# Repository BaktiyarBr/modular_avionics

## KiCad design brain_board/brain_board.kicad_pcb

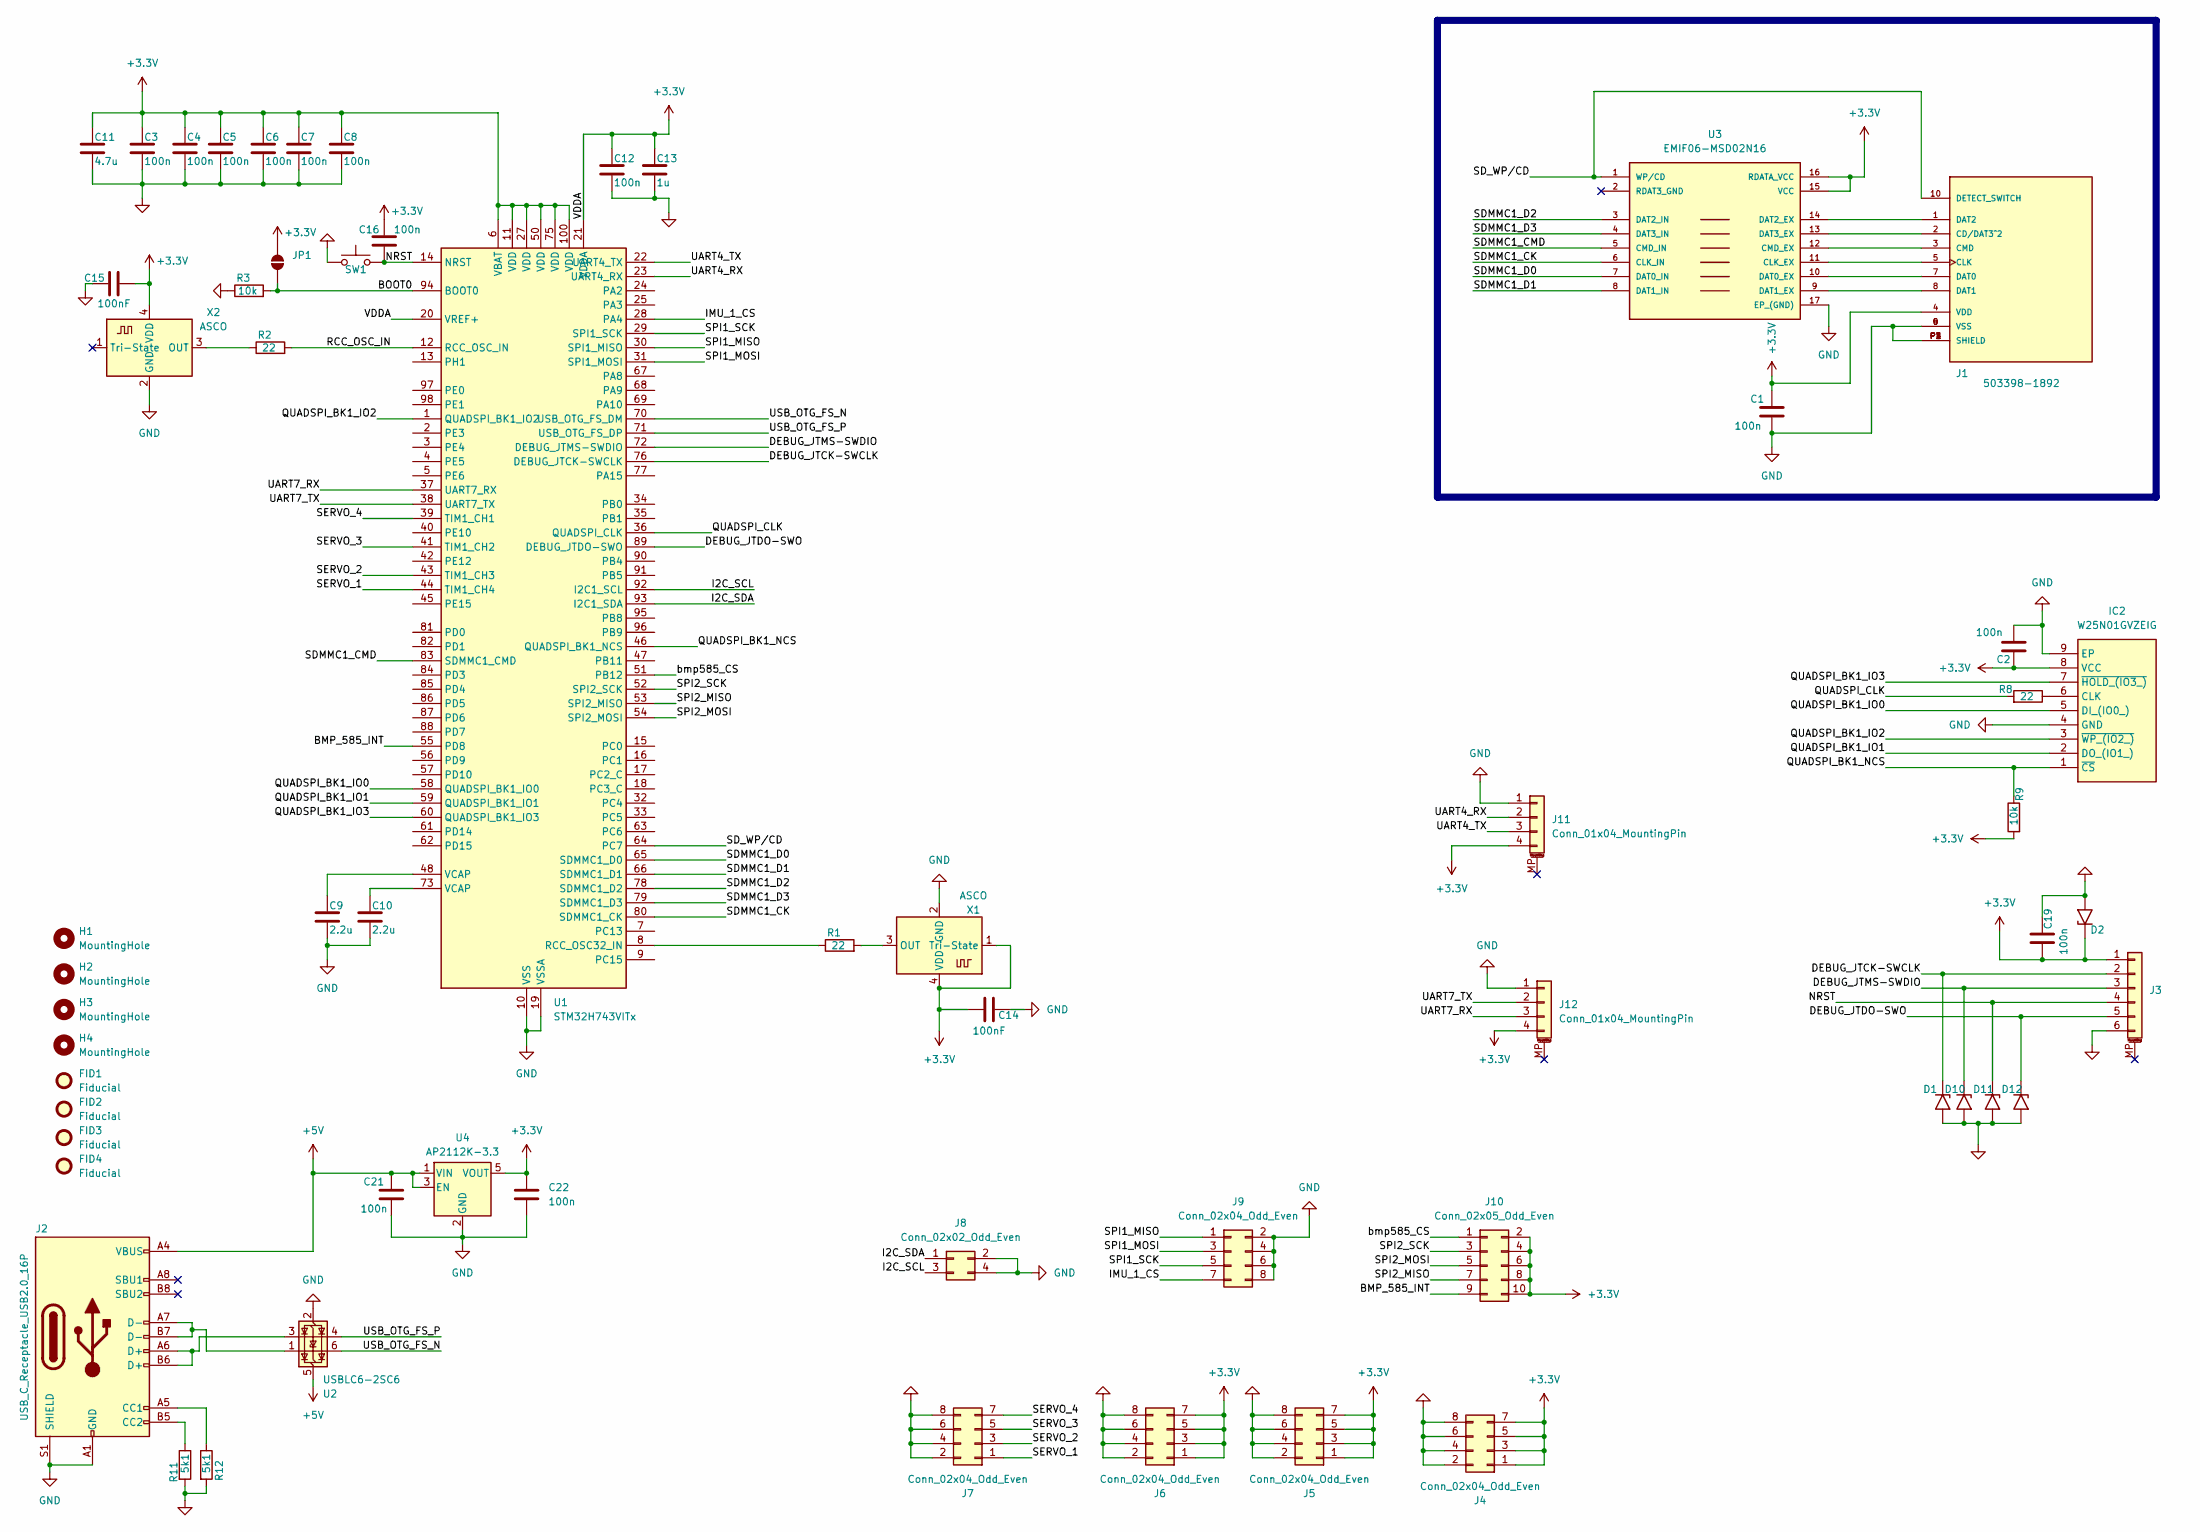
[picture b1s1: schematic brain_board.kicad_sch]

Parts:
C1, C2, C3, C4, C5, C6, C7, C8, C12, C16, C19: 100n; C_0603_1608Metric
C9, C10: 2.2u; C_0603_1608Metric
C11: 4.7u; C_0603_1608Metric
C13: 1u; C_0603_1608Metric
C14, C15: 100nF; C_0603_1608Metric
C21, C22: 100n; C_0603_1608Metric_Pad1.08x0.95mm_HandSolder
D1, D2, D10, D11, D12: 0603ESDA-05N; D_0402_1005Metric
FID1, FID2, FID3, FID4: Fiducial; Fiducial_0.5mm_Mask1mm
H1, H2, H3, H4: MountingHole; MountingHole_2.2mm_M2
IC2: W25N01GVZEIG; WSON-8-1EP_6x5mm_P1.27mm_EP3.4x4.3mm; Mouser Part Number 454-W25N01GVZEIG
J1: 503398-1892; MOLEX_503398-1892; PARTREV 0
J2: USB_C_Receptacle_USB2.0_16P; USB_C_Receptacle_HRO_TYPE-C-31-M-12
J3: Conn_01x06_MountingPin; JST_GH_SM06B-GHS-TB_1x06-1MP_P1.25mm_Horizontal
J4, J5, J6, J7, J9: Conn_02x04_Odd_Even; PinSocket_2x04_P2.54mm_Vertical_SMD
J8: Conn_02x02_Odd_Even; PinSocket_2x02_P2.54mm_Vertical_SMD
J10: Conn_02x05_Odd_Even; PinSocket_2x05_P2.54mm_Vertical_SMD
J11, J12: Conn_01x04_MountingPin; JST_GH_SM04B-GHS-TB_1x04-1MP_P1.25mm_Horizontal
JP1: SolderJumper_2_Open; SolderJumper-2_P1.3mm_Open_TrianglePad1.0x1.5mm
R1, R2, R8: 22; R_0603_1608Metric
R3, R9: 10k; R_0603_1608Metric
R11, R12: 5k1; R_0603_1608Metric
SW1: SW_Omron_B3FS; SW_Push_SPST_NO_Alps_SKRK
U1: STM32H743VITx; LQFP-100_14x14mm_P0.5mm
U2: USBLC6-2SC6; SOT-23-6
U3: EMIF06-MSD02N16; EMIF06MSD02N16; MOUSER_PART_NUMBER 511-EMIF06-MSD02N16
U4: AP2112K-3.3; SOT-23-5
X1, X2: ASCO; Oscillator_SMD_Abracon_ASCO-4Pin_1.6x1.2mm

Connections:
+3.3V: C1.1, C2.1, C3.1, C4.1, C5.1, C6.1, C7.1, C8.1, C11.1, C12.1, C13.1, C14.2, C15.2, C16.2, C19.2, C22.2, D2.1 (A1), IC2.8 (VCC), J1.4 (VDD), J3.1, J4.1, J4.3, J4.5, J4.7, J5.1, J5.3, J5.5, J5.7, J6.1, J6.3, J6.5, J6.7, J10.2, J10.4, J10.6, J10.8, J10.10, J11.4, J12.4, JP1.1 (A), R9.2, U1.6 (VBAT), U1.11 (VDD), U1.20 (VREF+), U1.21 (VDDA), U1.27 (VDD), U1.50 (VDD), U1.75 (VDD), U1.100 (VDD), U3.15 (VCC), U3.16 (RDATA_VCC), U4.5 (VOUT), X1.1 (Tri-State), X1.4 (VDD), X2.4 (VDD)
+5V: C21.1, J2.A4 (VBUS), J2.A9 (VBUS), J2.B4 (VBUS), J2.B9 (VBUS), U2.5 (VBUS), U4.1 (VIN), U4.3 (EN)
/BMP_585_INT: J10.9, U1.55 (PD8)
/BOOT0: JP1.2 (B), R3.2, U1.94 (BOOT0)
/DEBUG_JTCK-SWCLK: D1.1 (A1), J3.2, U1.76 (DEBUG_JTCK-SWCLK)
/DEBUG_JTDO-SWO: D12.1 (A1), J3.5, U1.89 (DEBUG_JTDO-SWO)
/DEBUG_JTMS-SWDIO: D10.1 (A1), J3.3, U1.72 (DEBUG_JTMS-SWDIO)
/I2C_SCL: J8.3, U1.92 (I2C1_SCL)
/I2C_SDA: J8.1, U1.93 (I2C1_SDA)
/IMU_1_CS: J9.7, U1.28 (PA4)
/NRST: C16.1, D11.1 (A1), J3.4, SW1.2, U1.14 (NRST)
/QUADSPI_BK1_IO0: IC2.5 (DI_(IO0_)), U1.58 (QUADSPI_BK1_IO0)
/QUADSPI_BK1_IO1: IC2.2 (DO_(IO1_)), U1.59 (QUADSPI_BK1_IO1)
/QUADSPI_BK1_IO2: IC2.3 (~WP_(IO2_)), U1.1 (QUADSPI_BK1_IO2)
/QUADSPI_BK1_IO3: IC2.7 (~HOLD_(IO3_)), U1.60 (QUADSPI_BK1_IO3)
/QUADSPI_BK1_NCS: IC2.1 (~CS), R9.1, U1.46 (QUADSPI_BK1_NCS)
/QUADSPI_CLK: R8.2, U1.36 (QUADSPI_CLK)
/RCC_OSC_IN: R2.2, U1.12 (RCC_OSC_IN)
/SDMMC1_CK: U1.80 (SDMMC1_CK), U3.6 (CLK_IN)
/SDMMC1_CMD: U1.83 (SDMMC1_CMD), U3.5 (CMD_IN)
/SDMMC1_D0: U1.65 (SDMMC1_D0), U3.7 (DAT0_IN)
/SDMMC1_D1: U1.66 (SDMMC1_D1), U3.8 (DAT1_IN)
/SDMMC1_D2: U1.78 (SDMMC1_D2), U3.3 (DAT2_IN)
/SDMMC1_D3: U1.79 (SDMMC1_D3), U3.4 (DAT3_IN)
/SD_WP/CD: J1.10 (DETECT_SWITCH), U1.64 (PC7), U3.1 (WP/CD)
/SERVO_1: J7.1, U1.44 (TIM1_CH4)
/SERVO_2: J7.3, U1.43 (TIM1_CH3)
/SERVO_3: J7.5, U1.41 (TIM1_CH2)
/SERVO_4: J7.7, U1.39 (TIM1_CH1)
/SPI1_MISO: J9.1, U1.30 (SPI1_MISO)
/SPI1_MOSI: J9.3, U1.31 (SPI1_MOSI)
/SPI1_SCK: J9.5, U1.29 (SPI1_SCK)
/SPI2_MISO: J10.7, U1.53 (SPI2_MISO)
/SPI2_MOSI: J10.5, U1.54 (SPI2_MOSI)
/SPI2_SCK: J10.3, U1.52 (SPI2_SCK)
/UART4_RX: J11.2, U1.23 (UART4_RX)
/UART4_TX: J11.3, U1.22 (UART4_TX)
/UART7_RX: J12.3, U1.37 (UART7_RX)
/UART7_TX: J12.2, U1.38 (UART7_TX)
/USB_OTG_FS_N: U1.70 (USB_OTG_FS_DM), U2.6 (I/O1)
/USB_OTG_FS_P: U1.71 (USB_OTG_FS_DP), U2.4 (I/O2)
/bmp585_CS: J10.1, U1.51 (PB12)
GND: C1.2, C2.2, C3.2, C4.2, C5.2, C6.2, C7.2, C8.2, C9.2, C10.2, C11.2, C12.2, C13.2, C14.1, C15.1, C19.1, C21.2, C22.1, D1.2 (A2), D2.2 (A2), D10.2 (A2), D11.2 (A2), D12.2 (A2), IC2.4 (GND), IC2.9 (EP), J1.6 (VSS), J1.9 (VSS), J1.P1 (SHIELD), J1.P2 (SHIELD), J1.P3 (SHIELD), J1.P4 (SHIELD), J2.A1 (GND), J2.A12 (GND), J2.B1 (GND), J2.B12 (GND), J2.S1 (SHIELD), J3.6, J4.2, J4.4, J4.6, J4.8, J5.2, J5.4, J5.6, J5.8, J6.2, J6.4, J6.6, J6.8, J7.2, J7.4, J7.6, J7.8, J8.2, J8.4, J9.2, J9.4, J9.6, J9.8, J11.1, J12.1, R3.1, R11.2, R12.2, SW1.1, U1.10 (VSS), U1.19 (VSSA), U1.26 (VSS), U1.49 (VSS), U1.74 (VSS), U1.99 (VSS), U2.2 (GND), U3.17 (EP_(GND)), U4.2 (GND), X1.2 (GND), X2.2 (GND)
unnamed: C9.1, U1.48 (VCAP)
unnamed: C10.1, U1.73 (VCAP)
unnamed: IC2.6 (CLK), R8.1
unnamed: J1.2 (CD/DAT3^2), U3.13 (DAT3_EX)
unnamed: J1.5 (CLK), U3.11 (CLK_EX)
unnamed: J1.3 (CMD), U3.12 (CMD_EX)
unnamed: J1.7 (DAT0), U3.10 (DAT0_EX)
unnamed: J1.8 (DAT1), U3.9 (DAT1_EX)
unnamed: J1.1 (DAT2), U3.14 (DAT2_EX)
unnamed: J2.A5 (CC1), R12.1
unnamed: J2.B5 (CC2), R11.1
unnamed: J2.A6 (D+), J2.B6 (D+), U2.3 (I/O2)
unnamed: J2.A7 (D-), J2.B7 (D-), U2.1 (I/O1)
unnamed: R1.1, U1.8 (RCC_OSC32_IN)
unnamed: R1.2, X1.3 (OUT)
unnamed: R2.1, X2.3 (OUT)

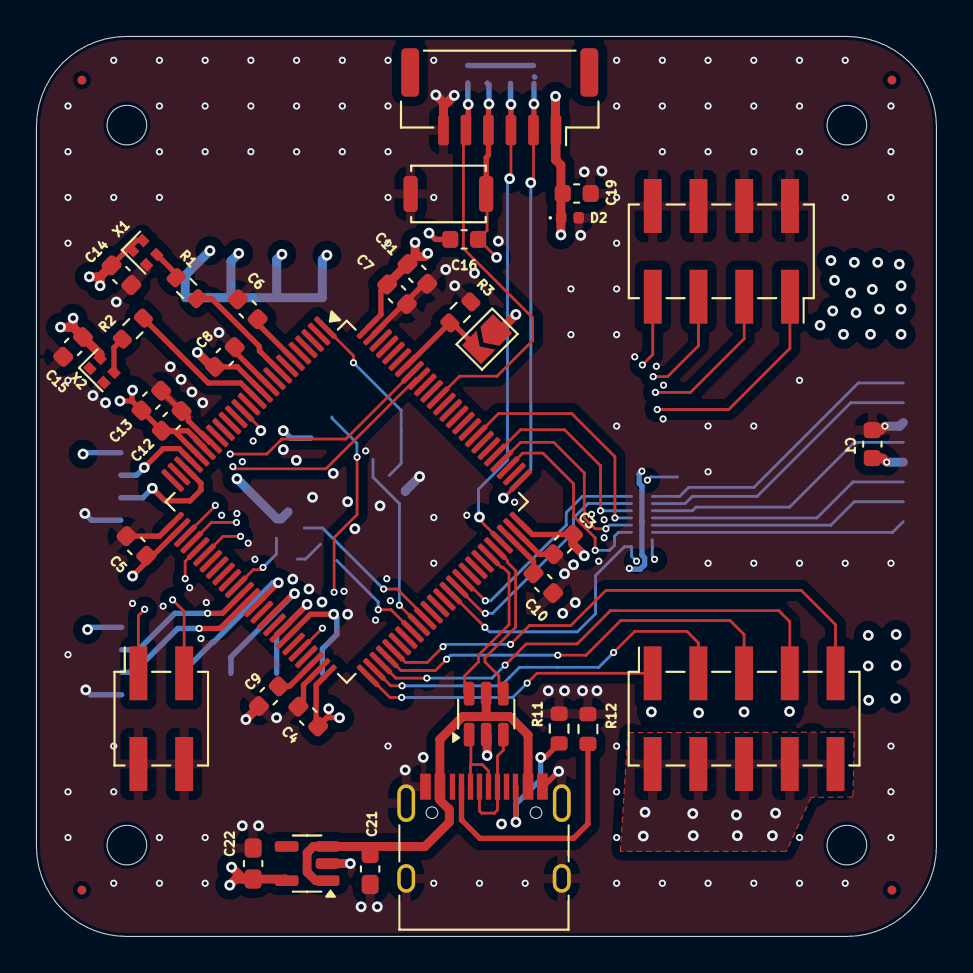
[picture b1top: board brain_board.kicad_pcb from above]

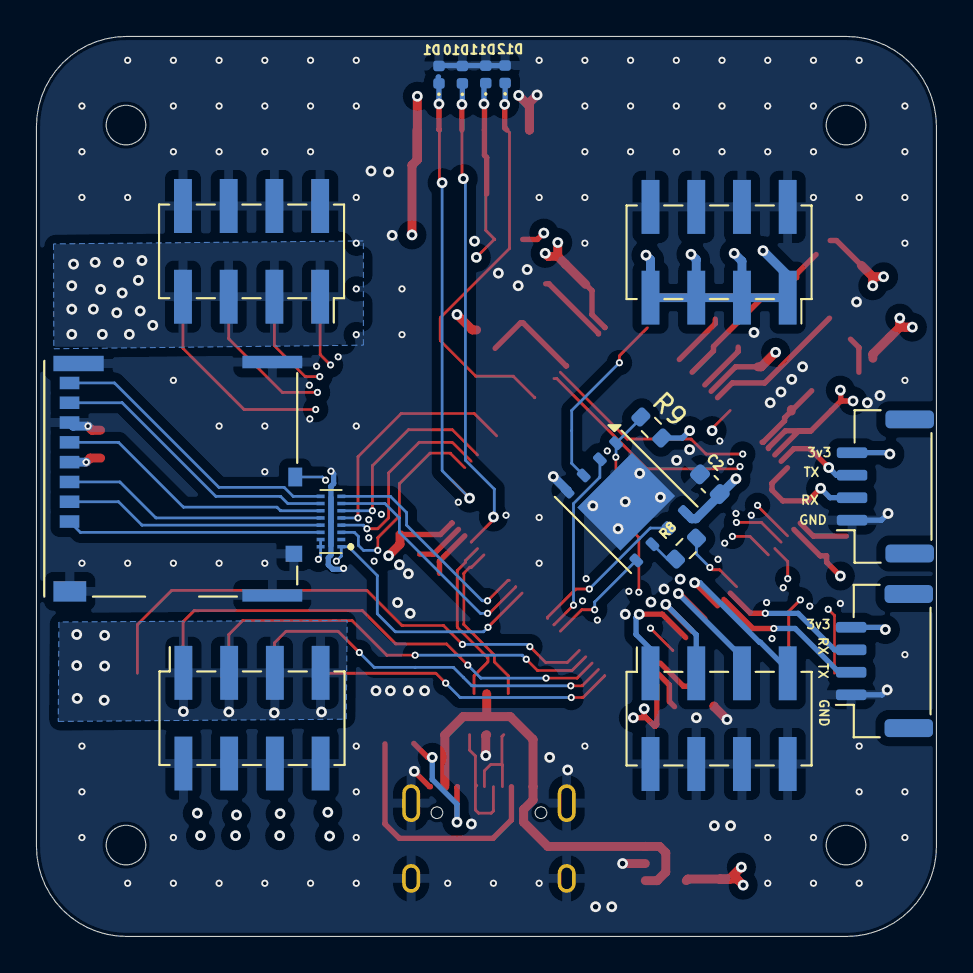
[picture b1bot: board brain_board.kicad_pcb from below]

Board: 6 copper layers, 50.0 x 50.0 mm, 60 parts (16 on the bottom side), 59 nets.

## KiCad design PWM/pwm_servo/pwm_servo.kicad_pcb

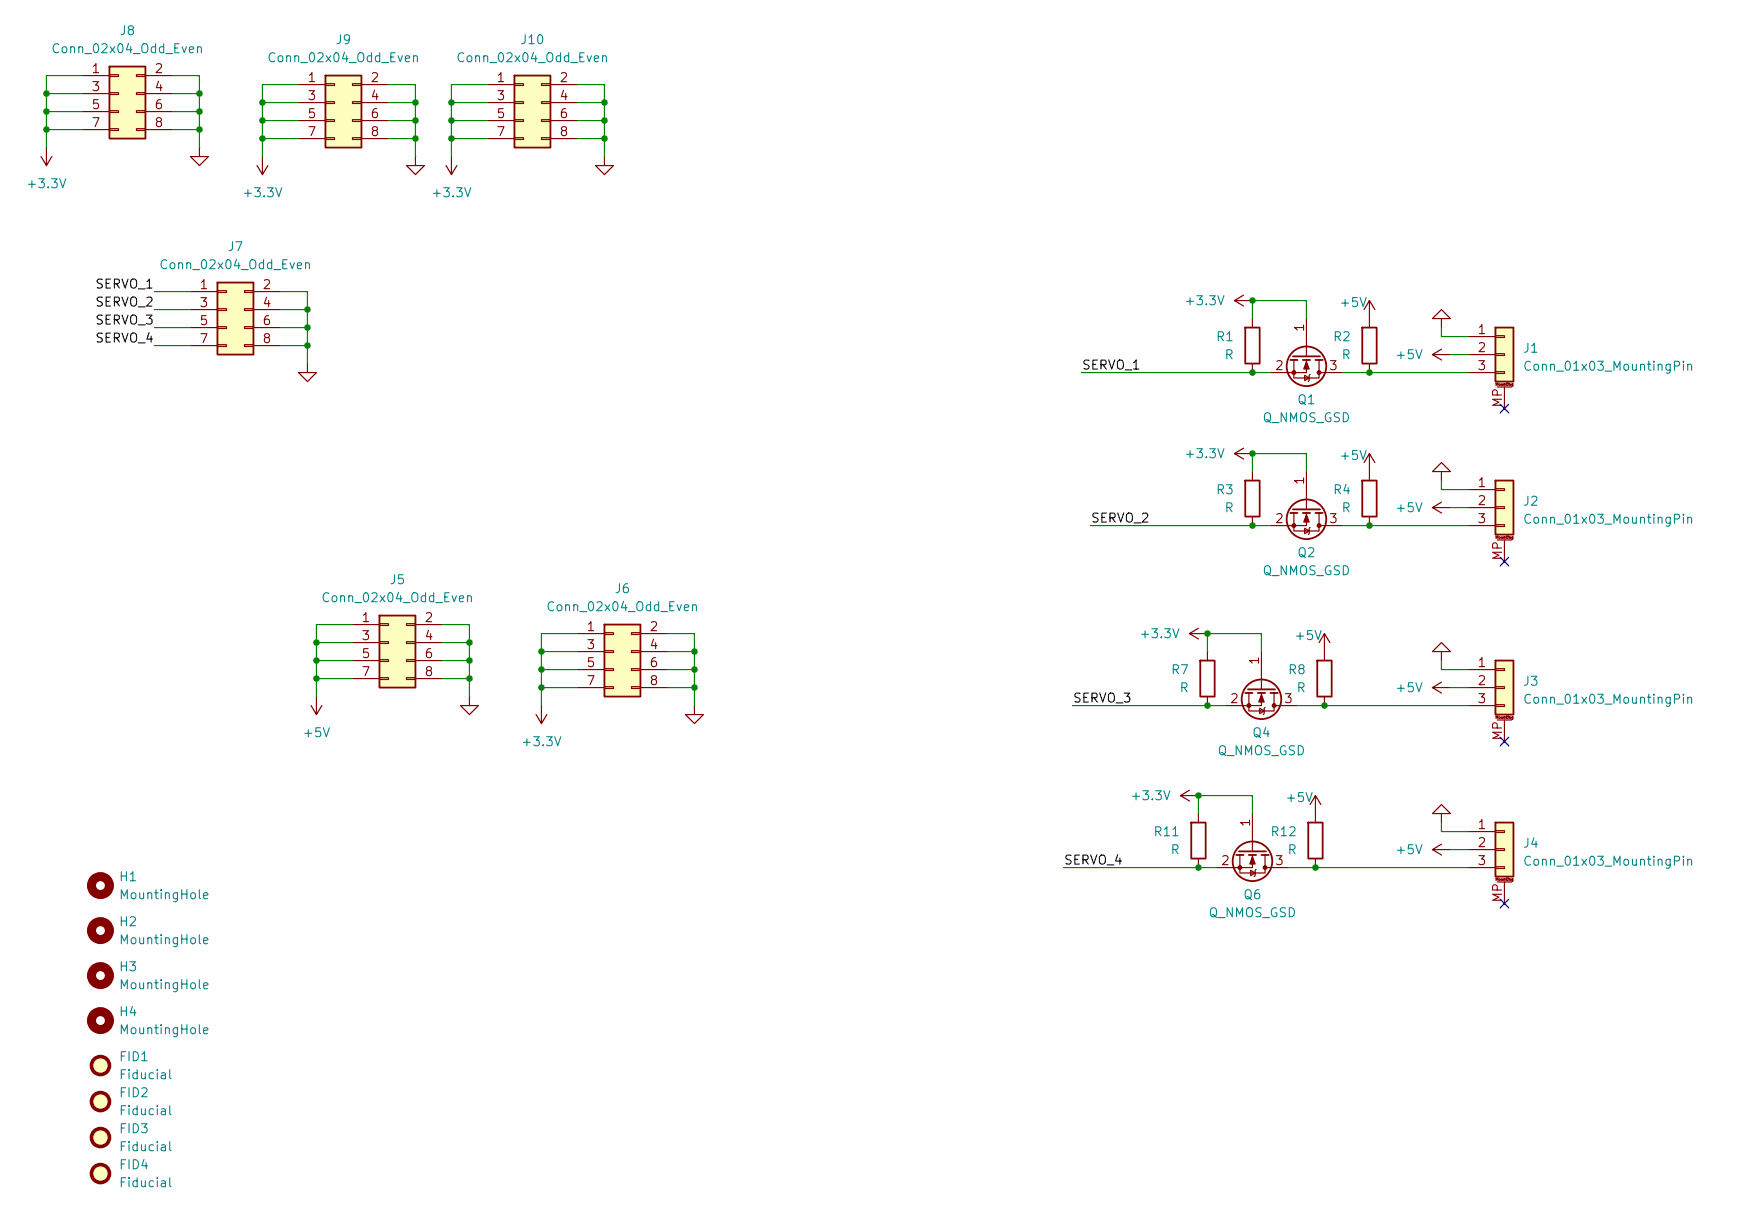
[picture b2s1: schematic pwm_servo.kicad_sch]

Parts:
FID1, FID2, FID3, FID4: Fiducial; Fiducial_0.5mm_Mask1mm
H1, H2, H3, H4: MountingHole; MountingHole_2.2mm_M2
J1, J2, J3, J4: Conn_01x03_MountingPin; JST_GH_SM03B-GHS-TB_1x03-1MP_P1.25mm_Horizontal
J5, J6, J7, J8, J9, J10: Conn_02x04_Odd_Even; PinSocket_2x04_P2.54mm_Vertical_SMD
Q1, Q2, Q4, Q6: Q_NMOS_GSD; SOT-23-3
R1, R2, R3, R4, R7, R8, R11, R12: R; R_0603_1608Metric_Pad0.98x0.95mm_HandSolder

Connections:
+3.3V: J6.1, J6.3, J6.5, J6.7, J8.1, J8.3, J8.5, J8.7, J9.1, J9.3, J9.5, J9.7, J10.1, J10.3, J10.5, J10.7, Q1.1 (G), Q2.1 (G), Q4.1 (G), Q6.1 (G), R1.2, R3.2, R7.2, R11.2
+5V: J1.2, J2.2, J3.2, J4.2, J5.1, J5.3, J5.5, J5.7, R2.2, R4.2, R8.2, R12.2
/SERVO_1: J7.1, Q1.2 (S), R1.1
/SERVO_2: J7.3, Q2.2 (S), R3.1
/SERVO_3: J7.5, Q4.2 (S), R7.1
/SERVO_4: J7.7, Q6.2 (S), R11.1
GND: J1.1, J2.1, J3.1, J4.1, J5.2, J5.4, J5.6, J5.8, J6.2, J6.4, J6.6, J6.8, J7.2, J7.4, J7.6, J7.8, J8.2, J8.4, J8.6, J8.8, J9.2, J9.4, J9.6, J9.8, J10.2, J10.4, J10.6, J10.8
unnamed: J1.3, Q1.3 (D), R2.1
unnamed: J2.3, Q2.3 (D), R4.1
unnamed: J3.3, Q4.3 (D), R8.1
unnamed: J4.3, Q6.3 (D), R12.1

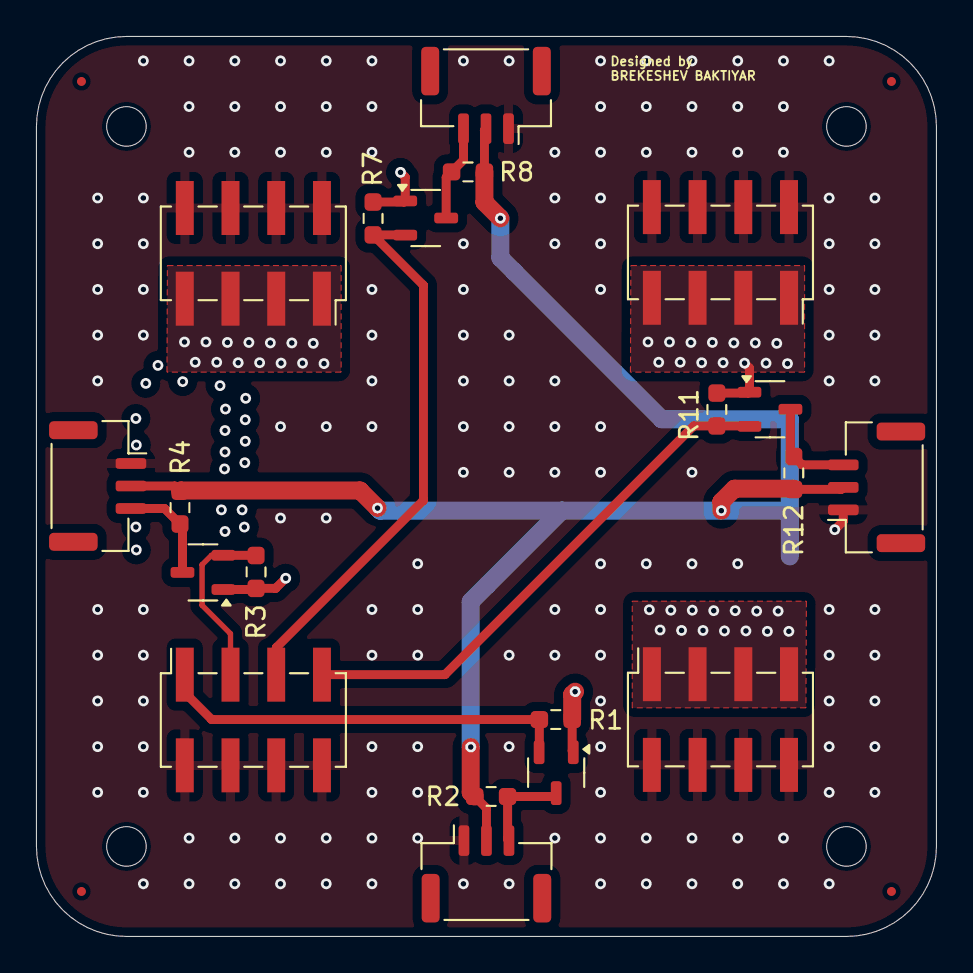
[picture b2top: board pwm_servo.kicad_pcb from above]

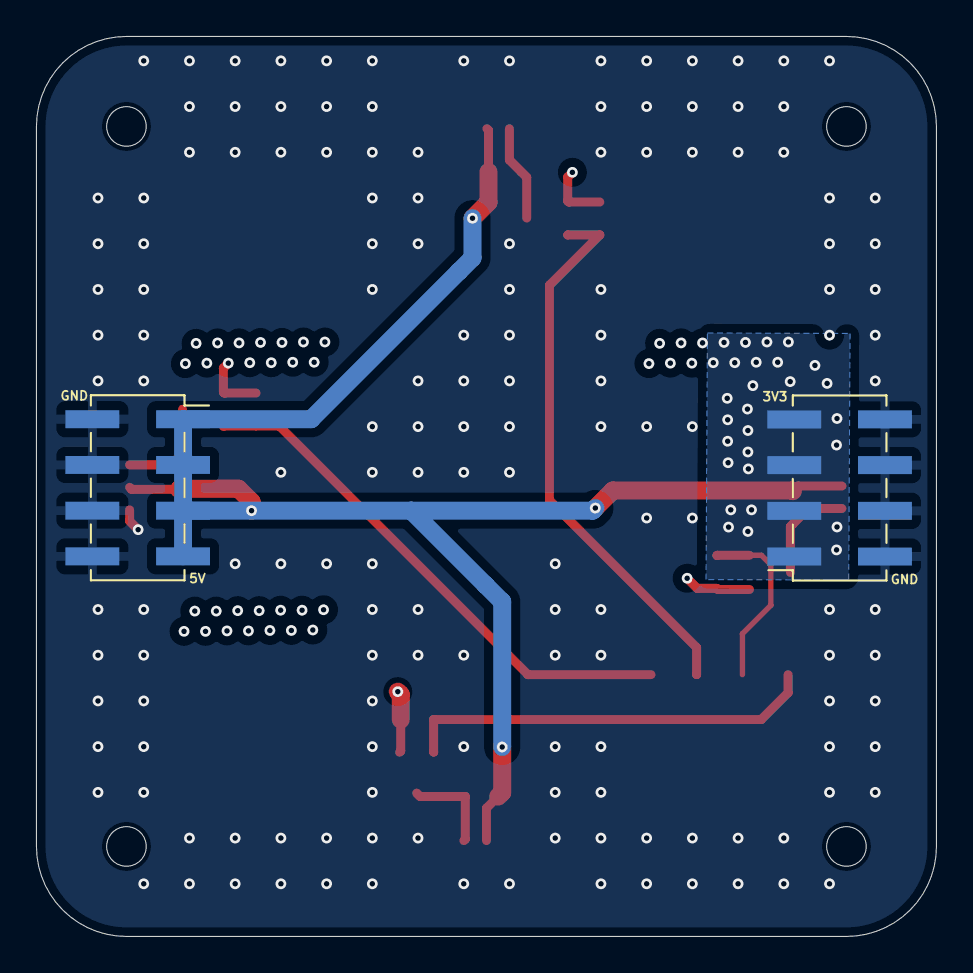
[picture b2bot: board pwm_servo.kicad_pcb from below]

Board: 4 copper layers, 50.0 x 50.0 mm, 30 parts (2 on the bottom side), 11 nets.

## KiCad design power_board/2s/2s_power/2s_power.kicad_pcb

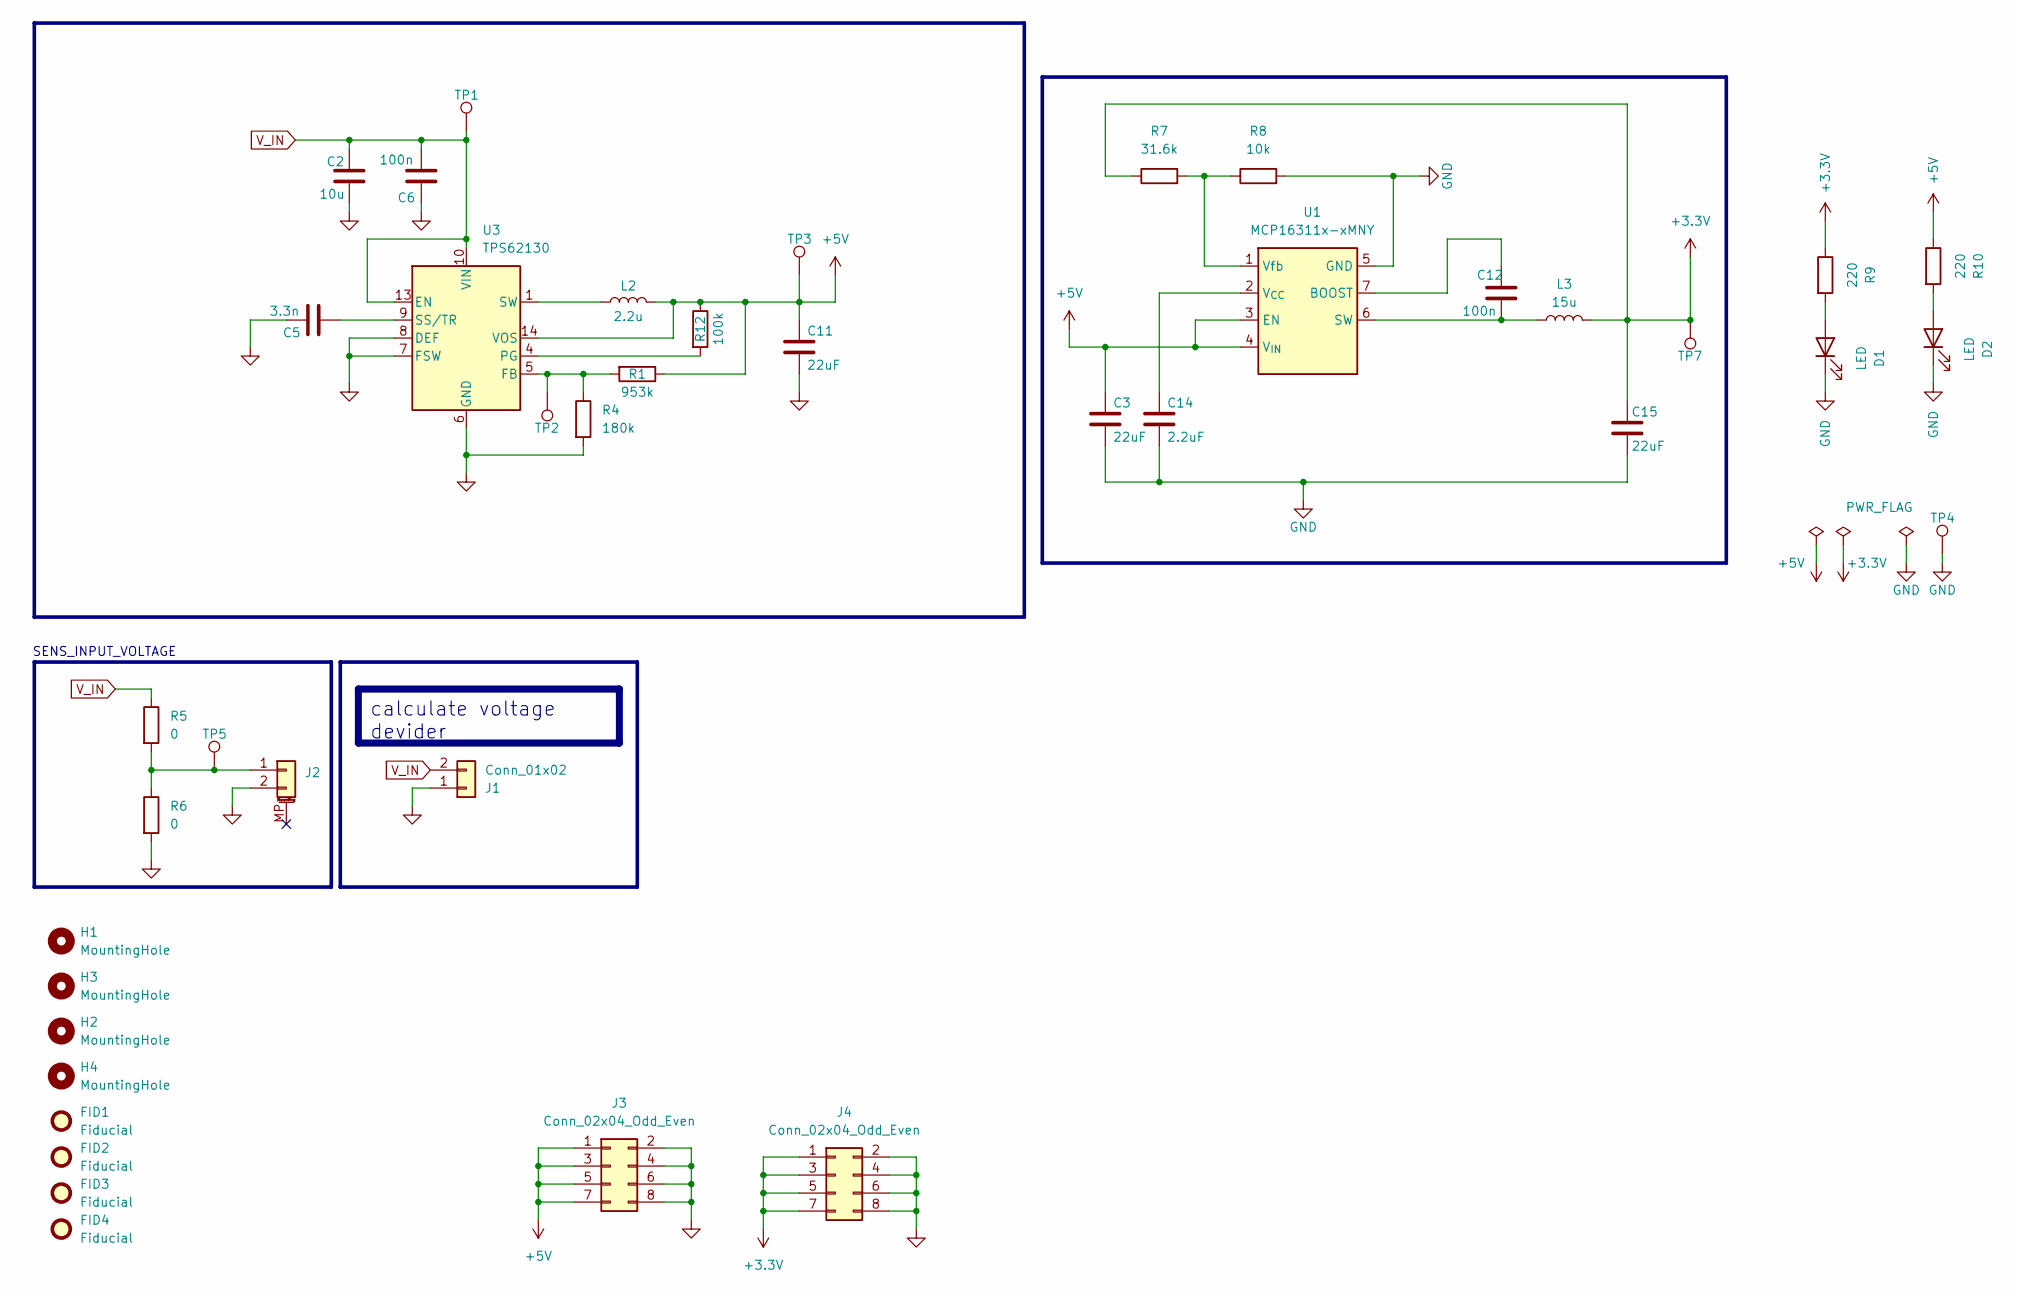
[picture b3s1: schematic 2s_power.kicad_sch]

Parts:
C2: 10u; C_1210_3225Metric
C3, C11, C15: 22uF; C_1210_3225Metric
C5: 3.3n; C_0603_1608Metric
C6, C12: 100n; C_0603_1608Metric
C14: 2.2uF; C_1210_3225Metric
D1, D2: LED; LED_0603_1608Metric_Pad1.05x0.95mm_HandSolder
FID1, FID2, FID3, FID4: Fiducial; Fiducial_0.5mm_Mask1mm
H1, H2, H3, H4: MountingHole; MountingHole_2.2mm_M2
J1: Conn_01x02; AMASS_XT30U-M_1x02_P5.0mm_Vertical
J2: Conn_01x02_MountingPin; JST_GH_SM02B-GHS-TB_1x02-1MP_P1.25mm_Horizontal
J3, J4: Conn_02x04_Odd_Even; PinSocket_2x04_P2.54mm_Vertical_SMD
L2: 2.2u; L_Chilisin_BMRF00101040
L3: 15u; L_Chilisin_BMRA00040415
R1: 953k; R_0603_1608Metric
R4: 180k; R_0603_1608Metric
R5, R6: 0; R_0603_1608Metric
R7: 31.6k; R_0603_1608Metric
R8: 10k; R_0603_1608Metric
R9, R10: 220; R_0603_1608Metric_Pad0.98x0.95mm_HandSolder
R12: 100k; R_0603_1608Metric
TP1, TP2, TP3, TP4, TP5, TP7: TestPoint; TestPoint_Pad_D1.0mm
U1: MCP16311x-xMNY; DFN-8-1EP_3x2mm_P0.5mm_EP1.75x1.45mm
U3: TPS62130; VQFN-16-1EP_3x3mm_P0.5mm_EP1.68x1.68mm_ThermalVias

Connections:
+3.3V: C15.1, J4.1, J4.3, J4.5, J4.7, L3.2, R7.1, R9.1, TP7.1
+5V: C3.1, C11.1, J3.1, J3.3, J3.5, J3.7, L2.2, R1.1, R10.1, R12.1, TP3.1, U1.3 (EN), U1.4 (V_{IN}), U3.14 (VOS)
GND: C2.2, C3.2, C5.1, C6.1, C11.2, C14.2, C15.2, D1.1 (K), D2.1 (K), J1.1, J2.2, J3.2, J3.4, J3.6, J3.8, J4.2, J4.4, J4.6, J4.8, R4.2, R6.2, R8.2, TP4.1, U1.5 (GND), U1.8 (GND), U1.9 (GND), U3.6 (GND), U3.7 (FSW), U3.8 (DEF), U3.15 (GND), U3.16 (GND), U3.17 (GND)
unnamed: D1.2 (A), R9.2
unnamed: D2.2 (A), R10.2
unnamed: J2.1, R5.2, R6.1, TP5.1
unnamed: L2.1, U3.1 (SW), U3.2 (SW), U3.3 (SW)
unnamed: C12.1, U1.7 (BOOST)
unnamed: C12.2, L3.1, U1.6 (SW)
unnamed: C14.1, U1.2 (V_{CC})
unnamed: R7.2, R8.1, U1.1 (Vfb)
unnamed: R1.2, R4.1, TP2.1, U3.5 (FB)
unnamed: R12.2, U3.4 (PG)
unnamed: C5.2, U3.9 (SS/TR)
V_IN: C2.1, C6.2, J1.2, R5.1, TP1.1, U3.10 (VIN), U3.11 (VIN), U3.12 (VIN), U3.13 (EN)

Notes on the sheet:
calculate voltage devider
SENS_INPUT_VOLTAGE

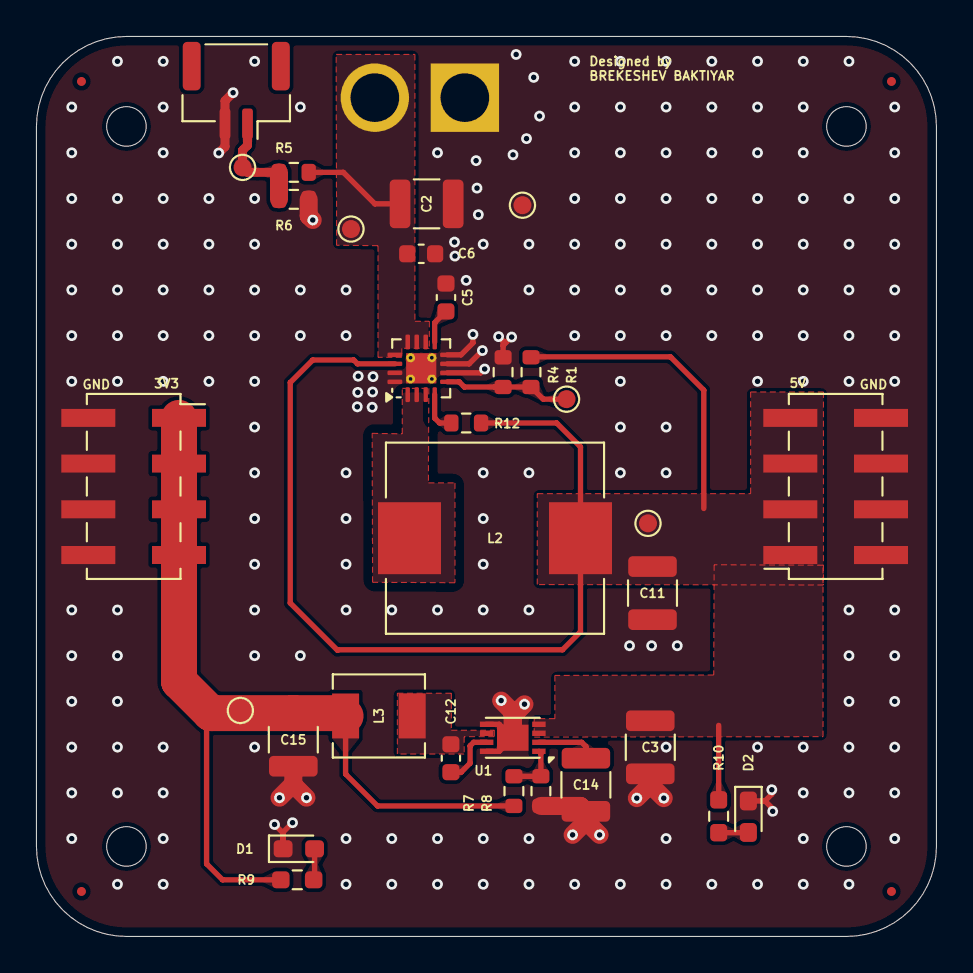
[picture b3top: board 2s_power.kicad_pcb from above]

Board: 2 copper layers, 50.0 x 50.0 mm, 41 parts (1 on the bottom side), 15 nets.

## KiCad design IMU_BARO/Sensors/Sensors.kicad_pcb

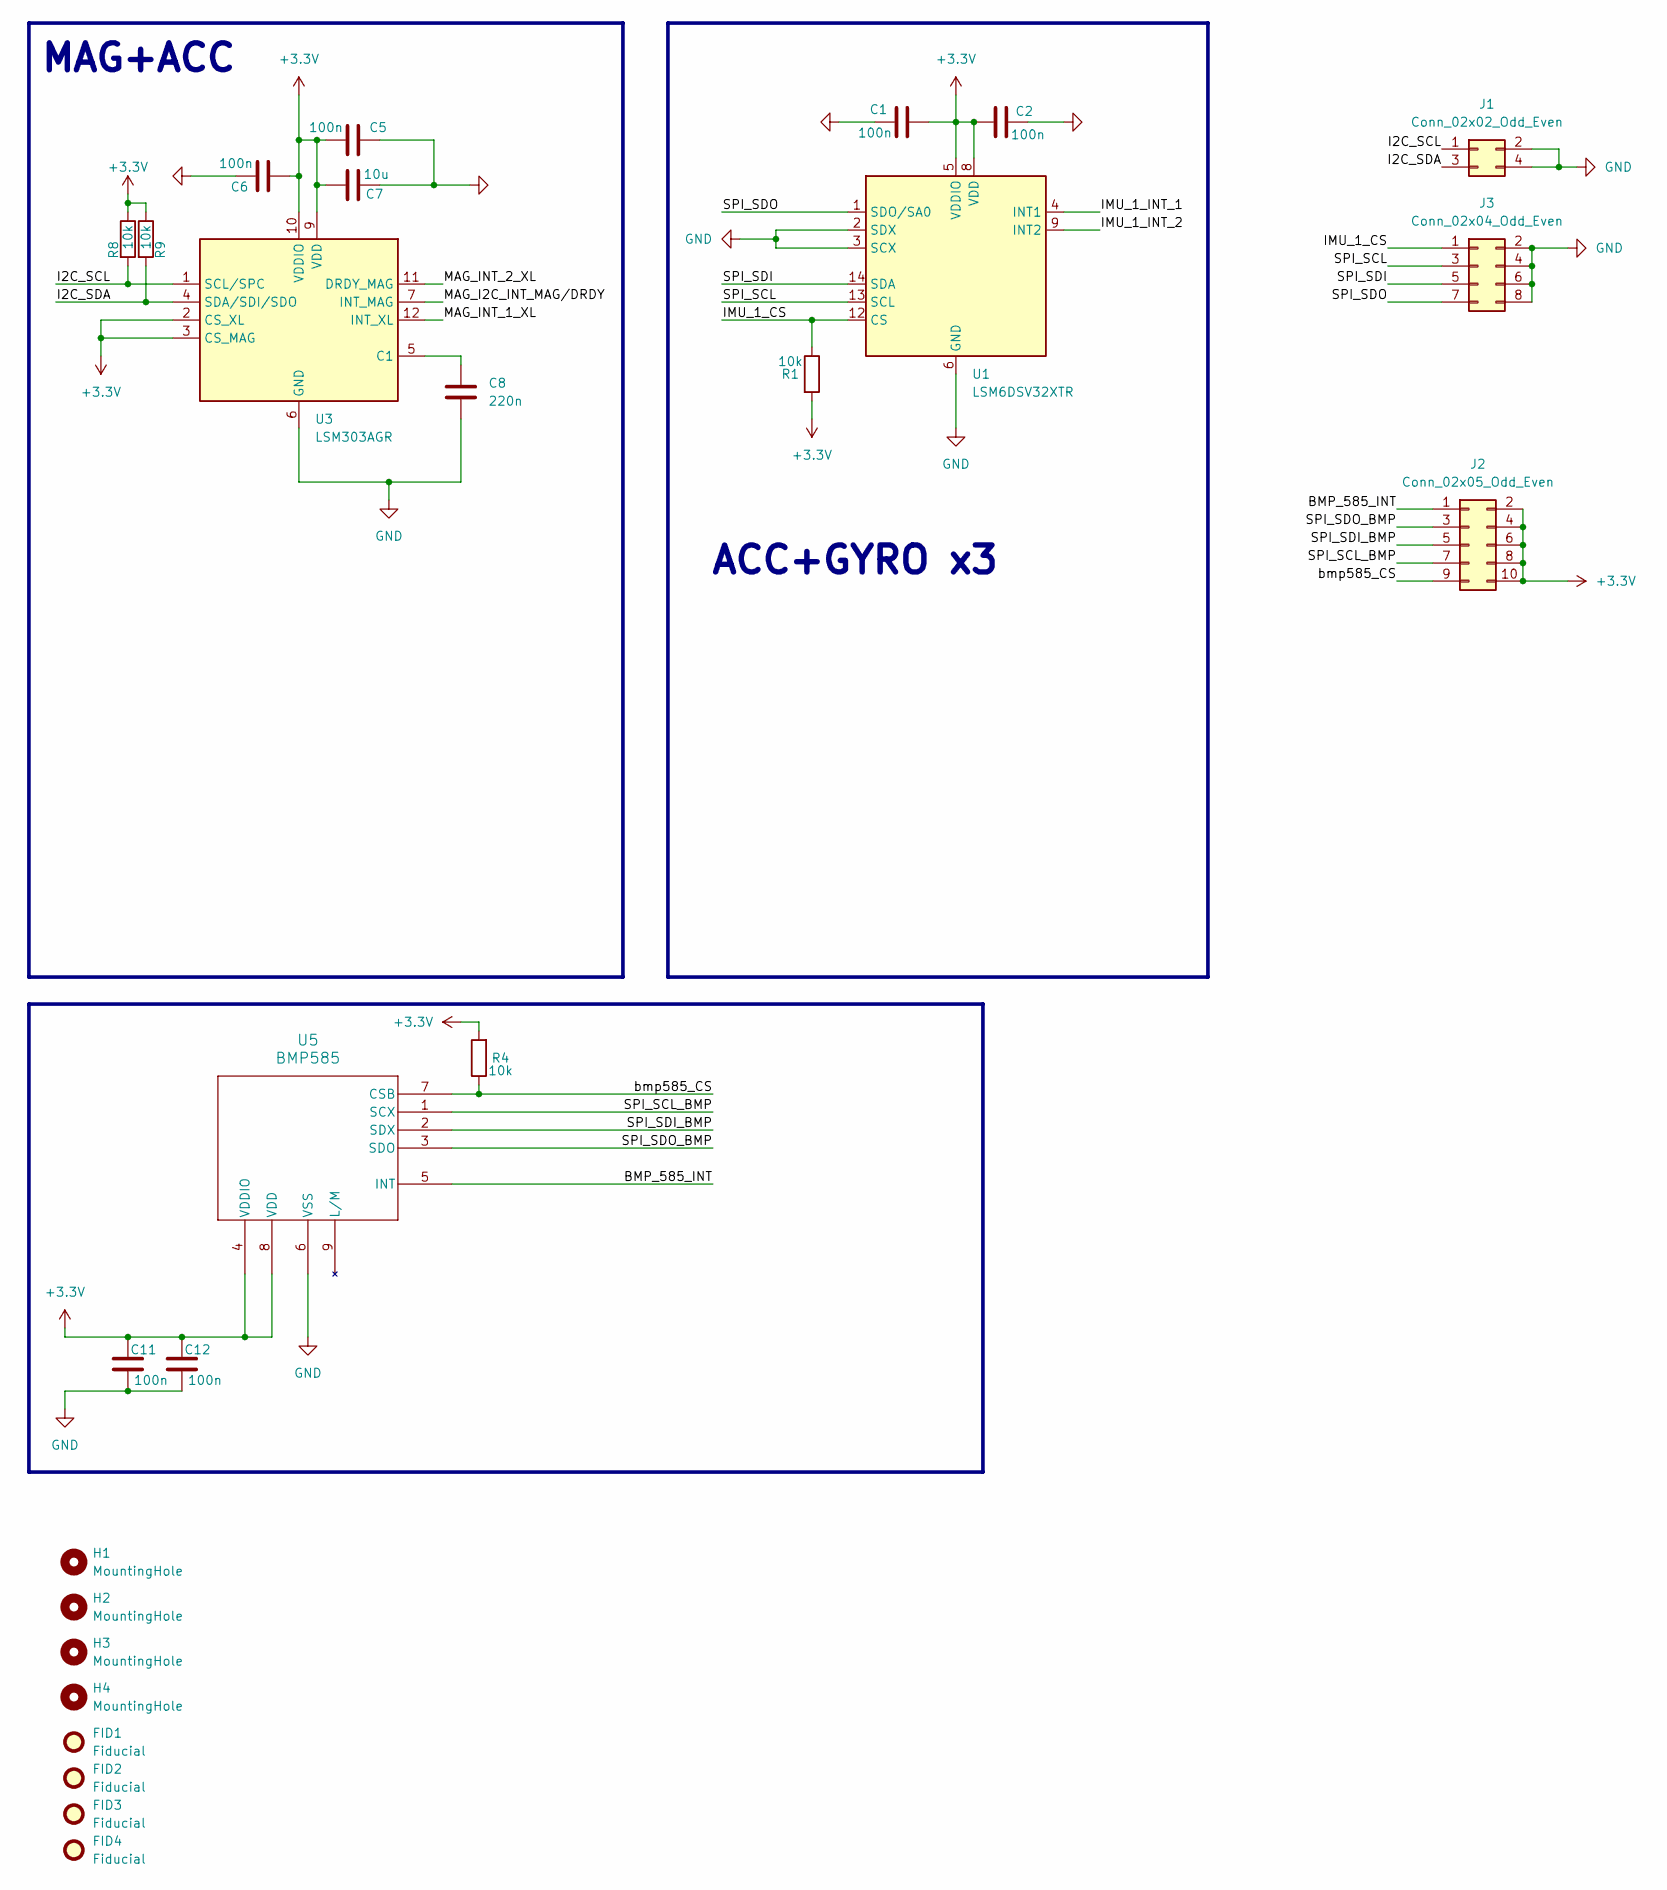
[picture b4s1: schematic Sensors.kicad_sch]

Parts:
C1, C2, C5, C6, C11, C12: 100n; C_0603_1608Metric
C7: 10u; C_0603_1608Metric
C8: 220n; C_0603_1608Metric
FID1, FID2, FID3, FID4: Fiducial; Fiducial_0.5mm_Mask1mm
H1, H2, H3, H4: MountingHole; MountingHole_2.2mm_M2
J1: Conn_02x02_Odd_Even; PinSocket_2x02_P2.54mm_Vertical_SMD
J2: Conn_02x05_Odd_Even; PinSocket_2x05_P2.54mm_Vertical_SMD
J3: Conn_02x04_Odd_Even; PinSocket_2x04_P2.54mm_Vertical_SMD
R1, R4, R8, R9: 10k; R_0603_1608Metric
U1: LSM6DSV32XTR; LGA-14_3x2.5mm_P0.5mm_LayoutBorder3x4y
U3: LSM303AGR; LGA-12_2x2mm_P0.5mm
U5: BMP585; LGA9_BMP585_BOS

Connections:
+3.3V: C1.2, C2.1, C5.2, C6.1, C7.2, C11.1, C12.1, J2.2, J2.4, J2.6, J2.8, J2.10, R1.2, R4.2, R8.1, R9.1, U1.5 (VDDIO), U1.8 (VDD), U3.2 (CS_XL), U3.3 (CS_MAG), U3.9 (VDD), U3.10 (VDDIO), U5.4 (VDDIO), U5.8 (VDD)
/BMP_585_INT: J2.1, U5.5 (INT)
/I2C_SCL: J1.1, R8.2, U3.1 (SCL/SPC)
/I2C_SDA: J1.3, R9.2, U3.4 (SDA/SDI/SDO)
/IMU_1_CS: J3.1, R1.1, U1.12 (CS)
/IMU_1_INT_1: U1.4 (INT1)
/IMU_1_INT_2: U1.9 (INT2)
/MAG_I2C_INT_MAG/DRDY: U3.7 (INT_MAG)
/MAG_INT_1_XL: U3.12 (INT_XL)
/MAG_INT_2_XL: U3.11 (DRDY_MAG)
/SPI_SCL: J3.3, U1.13 (SCL)
/SPI_SCL_BMP: J2.7, U5.1 (SCX)
/SPI_SDI: J3.5, U1.14 (SDA)
/SPI_SDI_BMP: J2.5, U5.2 (SDX)
/SPI_SDO: J3.7, U1.1 (SDO/SA0)
/SPI_SDO_BMP: J2.3, U5.3 (SDO)
/bmp585_CS: J2.9, R4.1, U5.7 (CSB)
GND: C1.1, C2.2, C5.1, C6.2, C7.1, C8.2, C11.2, C12.2, J1.2, J1.4, J3.2, J3.4, J3.6, J3.8, U1.2 (SDX), U1.3 (SCX), U1.6 (GND), U1.7 (GND), U3.6 (GND), U3.8 (GND), U5.6 (VSS)
unnamed: C8.1, U3.5 (C1)

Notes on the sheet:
ACC+GYRO x3
MAG+ACC
